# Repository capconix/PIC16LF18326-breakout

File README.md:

# PIC16LF18326-breakout
Breakout board for 16 pin UQFN PIC16LF18326

I had a need to use the PIC16LF18326 but also needed to use the 16UQFN package, so here is a breakout board that lets you plug this board into a breadboard!

This board was designed in KiCAD.

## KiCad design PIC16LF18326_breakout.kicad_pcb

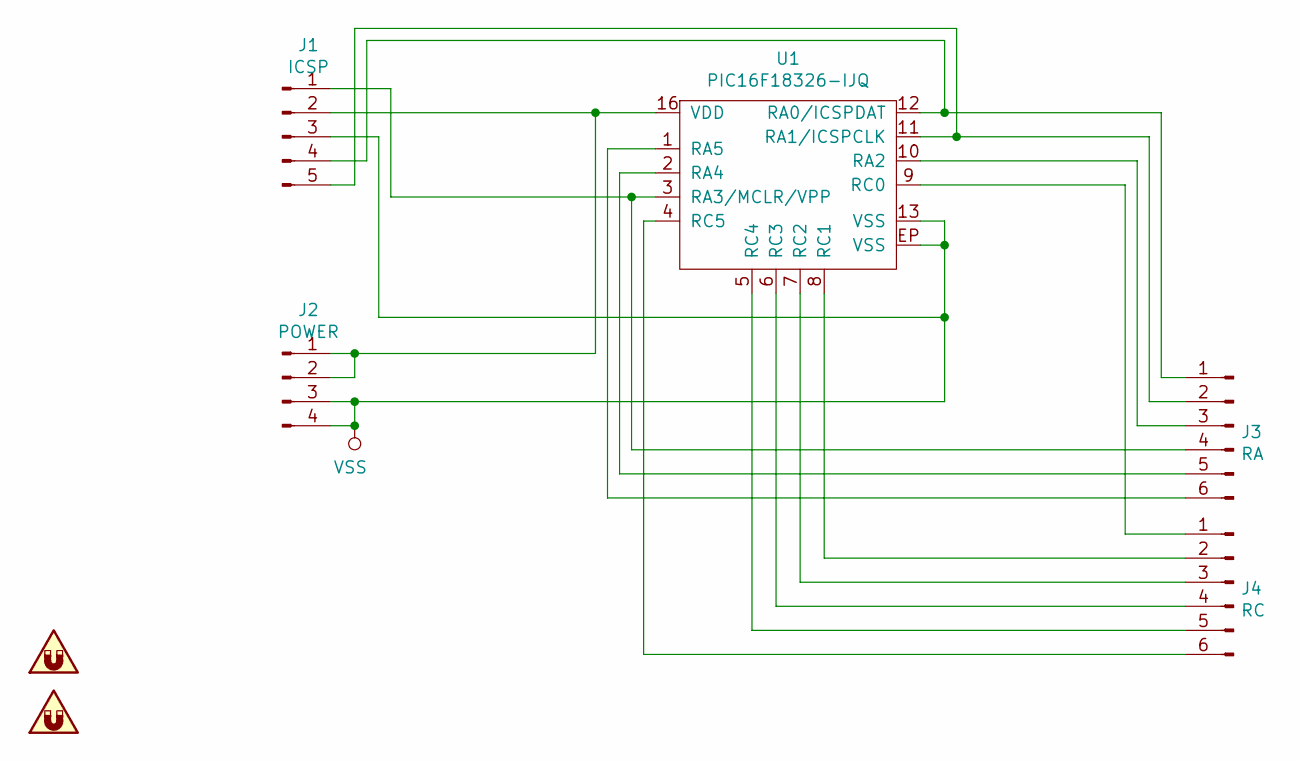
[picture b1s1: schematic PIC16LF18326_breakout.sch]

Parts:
J1: ICSP; PinSocket_1x05_P2.54mm_Vertical
J2: POWER; PinSocket_1x04_P2.54mm_Vertical
J3: RA; PinSocket_1x06_P2.54mm_Vertical
J4: RC; PinSocket_1x06_P2.54mm_Vertical
LOGO1: SYM_Magnet_Small; CapConiX_Logo_10_7
LOGO2: SYM_Magnet_Small; OSHW-Logo_5.7x6mm_SilkScreen
U1: PIC16F18326-IJQ; PIC16LF18326IJQ

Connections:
unnamed: J1.1, J3.4, U1.3 (RA3/MCLR/VPP)
unnamed: J1.2, J2.1, J2.2, U1.16 (VDD)
unnamed: J1.4, J3.1, U1.12 (RA0/ICSPDAT)
unnamed: J1.5, J3.2, U1.11 (RA1/ICSPCLK)
unnamed: J3.3, U1.10 (RA2)
unnamed: J3.5, U1.2 (RA4)
unnamed: J3.6, U1.1 (RA5)
unnamed: J4.1, U1.9 (RC0)
unnamed: J4.2, U1.8 (RC1)
unnamed: J4.3, U1.7 (RC2)
unnamed: J4.4, U1.6 (RC3)
unnamed: J4.5, U1.5 (RC4)
unnamed: J4.6, U1.4 (RC5)
VSS: J1.3, J2.3, J2.4, U1.13 (VSS), U1.EP (VSS)

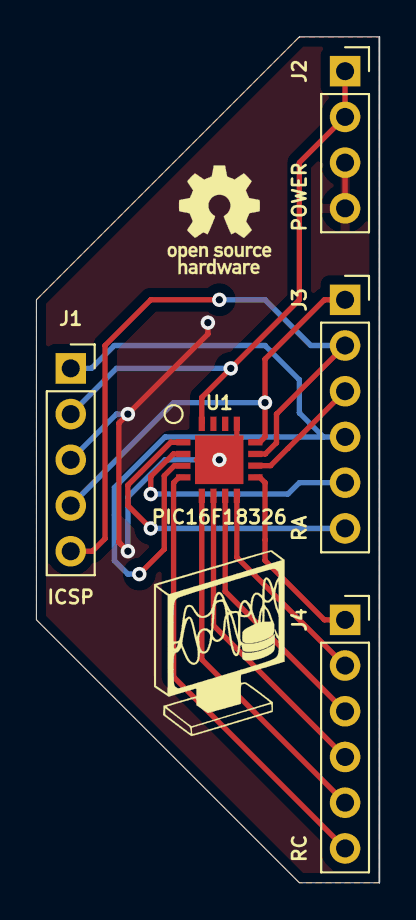
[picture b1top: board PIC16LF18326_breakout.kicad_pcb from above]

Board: 2 copper layers, 19.1 x 47.0 mm, 7 parts (0 on the bottom side), 14 nets.

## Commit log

2020-01-16 Added drawing files, ready to print
2020-01-16 Packaged up CAM files
